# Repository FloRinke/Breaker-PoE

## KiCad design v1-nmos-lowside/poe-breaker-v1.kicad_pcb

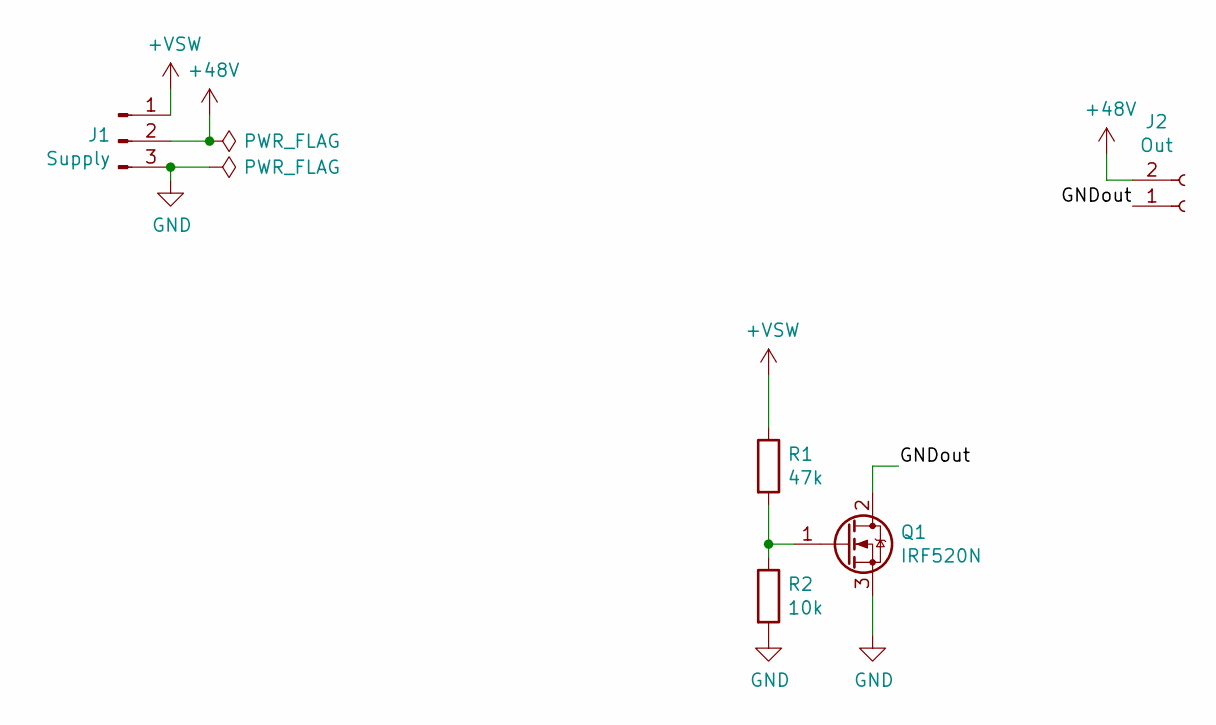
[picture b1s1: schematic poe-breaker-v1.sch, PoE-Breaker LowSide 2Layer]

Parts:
J1: Supply; TerminalBlock_Phoenix_MKDS-1,5-3-5.08_1x03_P5.08mm_Horizont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
J2: Out; TerminalBlock_Phoenix_MKDS-1,5-2-5.08_1x02_P5.08mm_Horizont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
Q1: IRF520N; TO-220-3_Horizontal_TabDown
R1: 47k; R_Axial_DIN0204_L3.6mm_D1.6mm_P5.08mm_Horizontal
R2: 10k; R_Axial_DIN0204_L3.6mm_D1.6mm_P5.08mm_Horizontal

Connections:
+48V: J1.2, J2.2
+VSW: J1.1, R1.1
/GNDout: J2.1, Q1.2 (D)
GND: J1.3, Q1.3 (S), R2.2
unnamed: Q1.1 (G), R1.2, R2.1

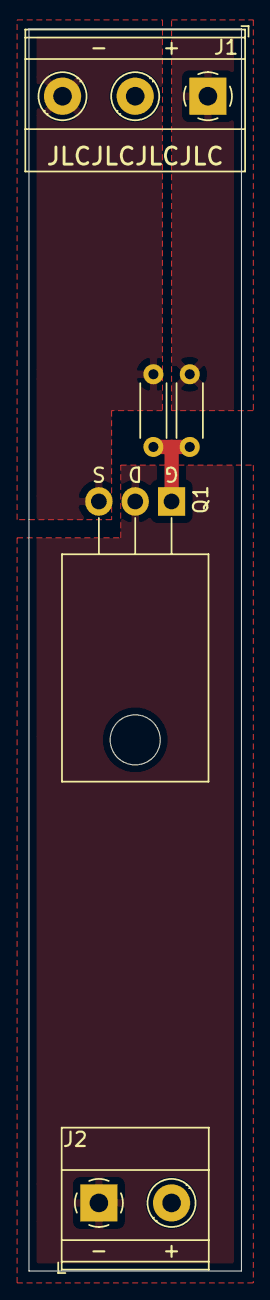
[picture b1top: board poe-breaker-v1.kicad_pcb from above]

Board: 2 copper layers, 14.8 x 86.8 mm, 5 parts (0 on the bottom side), 5 nets.

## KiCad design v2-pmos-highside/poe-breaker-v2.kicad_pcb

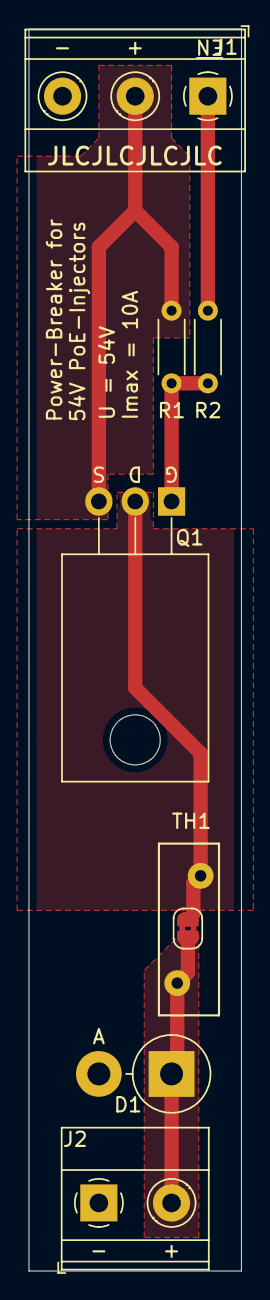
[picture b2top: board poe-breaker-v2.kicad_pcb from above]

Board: 2 copper layers, 14.8 x 86.8 mm, 8 parts (0 on the bottom side), 6 nets.

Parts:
D1: 1N5404; D_DO-201AD_P5.08mm_Vertical_AnodeUp
J1: Supply; TerminalBlock_Phoenix_MKDS-1,5-3-5.08_1x03_P5.08mm_Horizont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
J2: Out; TerminalBlock_Phoenix_MKDS-1,5-2-5.08_1x02_P5.08mm_Horizont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
JP1: Bypass; SolderJumper-2_P1.3mm_Bridged2Bar_RoundedPad1.0x1.5mm
Q1: IRF9530N; TO-220-3_Horizontal_TabDown
R1: 10k; R_Axial_DIN0204_L3.6mm_D1.6mm_P5.08mm_Horizontal
R2: 47k; R_Axial_DIN0204_L3.6mm_D1.6mm_P5.08mm_Horizontal
TH1: Thermistor_NTC; RV_Disc_D12mm_W4.2mm_P7.5mm

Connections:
+48V: J1.2, Q1.3, R1.1
/Gate: Q1.1, R1.2, R2.1
/Vout: D1.1, J2.2, JP1.2, TH1.2
/nEN: J1.1, R2.2
GND: D1.2, J1.3, J2.1
unnamed: JP1.1, Q1.2, TH1.1

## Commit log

2021-07-05 add metadata
2021-07-05 add nmos variant
2021-07-05 add pmos variant
2021-07-05 add pmos 1layer variant
2021-07-05 add page metadata

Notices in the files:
v1-nmos-lowside/poe-breaker-v1.sch:
http://creativecommons.org/licenses/by-nc-sa/4.0
